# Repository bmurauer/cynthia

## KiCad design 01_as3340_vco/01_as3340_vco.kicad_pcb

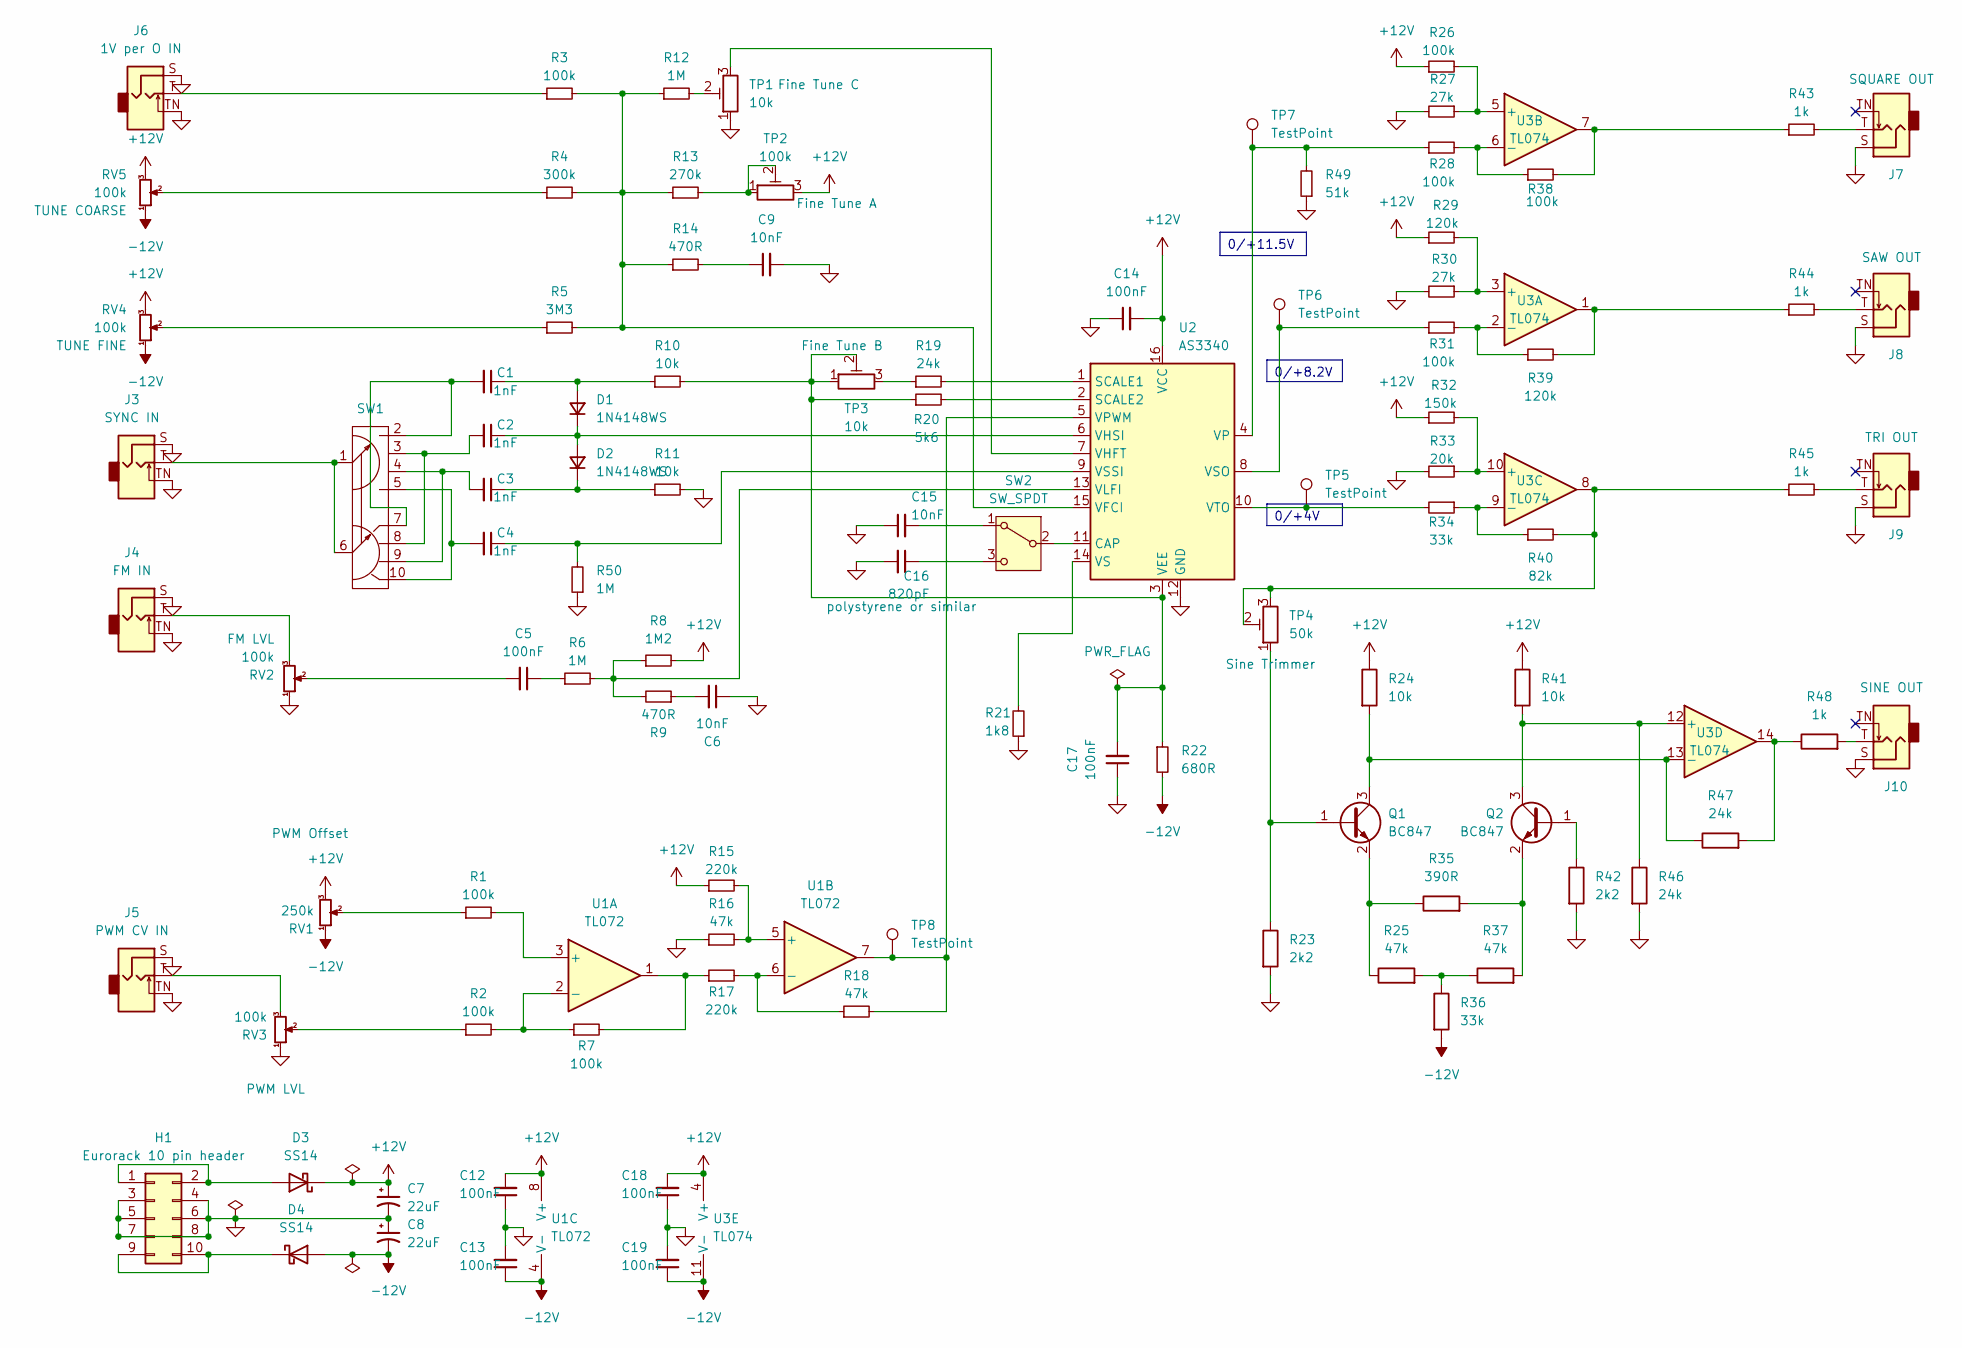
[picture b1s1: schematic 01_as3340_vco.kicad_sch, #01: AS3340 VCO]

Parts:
C1, C2, C3, C4: 1nF; C SMD 0805
C5, C12, C13, C14, C17, C18, C19: 100nF; C SMD 0805
C6, C9: 10nF; C SMD 0805
C7, C8: 22uF; CP_Radial_D6.3mm_P2.50mm
C15: 10nF; C_Disc_D10.5mm_W5.0mm_P10.00mm
C16: 820pF; C_Disc_D10.5mm_W5.0mm_P10.00mm
D1, D2: 1N4148WS; D_SOD-323_HandSoldering
D3, D4: SS14; D_SMA
H1: Eurorack 10 pin header; Eurorack Header
J3: SYNC IN; 3.5mm jack mono switched
J4: FM IN; 3.5mm jack mono switched
J5: PWM CV IN; 3.5mm jack mono switched
J6: 1V per O IN; 3.5mm jack mono switched
J7: SQUARE OUT; 3.5mm jack mono switched
J8: SAW OUT; 3.5mm jack mono switched
J9: TRI OUT; 3.5mm jack mono switched
J10: SINE OUT; 3.5mm jack mono switched
Q1, Q2: BC847; SOT-23
R1, R2, R3, R7, R26, R28, R31, R38: 100k; R SMD 0805
R4: 300k; R SMD 0805
R5: 3M3; R SMD 0805
R6, R12, R50: 1M; R SMD 0805
R8: 1M2; R SMD 0805
R9, R14: 470R; R SMD 0805
R10, R11, R24, R41: 10k; R SMD 0805
R13: 270k; R SMD 0805
R15, R17: 220k; R SMD 0805
R16, R18, R25, R37: 47k; R SMD 0805
R19, R46, R47: 24k; R SMD 0805
R20: 5k6; R SMD 0805
R21: 1k8; R SMD 0805
R22: 680R; R SMD 0805
R23, R42: 2k2; R SMD 0805
R27, R30: 27k; R SMD 0805
R29, R39: 120k; R SMD 0805
R32: 150k; R SMD 0805
R33: 20k; R SMD 0805
R34, R36: 33k; R SMD 0805
R35: 390R; R SMD 0805
R40: 82k; R SMD 0805
R43, R44, R45, R48: 1k; R SMD 0805
R49: 51k; R SMD 0805
RV1: 250k; potientiometer
RV2, RV3, RV4, RV5: 100k; potientiometer
SW1: switch_linear_2x4
SW2: SW_SPDT; switch_spdt
TP1, TP3: 10k; trimmer
TP2: 100k; trimmer
TP4: 50k; trimmer
TP5, TP6, TP7, TP8: TestPoint; TestPoint_Pad_1.0x1.0mm
U1: TL072; SOIC-8_3.9x4.9mm_P1.27mm
U2: AS3340; SOIC-16_3.9x9.9mm_P1.27mm
U3: TL074; SOIC-14_3.9x8.7mm_P1.27mm

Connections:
+12V: C7.1, C12.2, C14.2, C18.2, D3.1 (K), R8.2, R15.1, R24.1, R26.1, R29.1, R32.1, R41.1, RV1.3, RV4.3, RV5.3, TP2.3, U1.8 (V+), U2.16 (VCC), U3.4 (V+)
-12V: C8.2, C13.1, C19.1, D4.2 (A), R22.2, R36.2, RV1.1, RV4.1, RV5.1, U1.4 (V-), U3.11 (V-)
GND: C6.1, C7.2, C8.1, C9.2, C12.1, C13.2, C14.1, C15.1, C16.2, C17.1, C18.1, C19.2, H1.3, H1.4, H1.5, H1.6, H1.7, H1.8, J3.S, J3.TN, J4.S, J4.TN, J5.S, J5.TN, J6.S, J6.TN, J7.S, J8.S, J9.S, J10.S, R11.2, R16.1, R21.1, R23.2, R27.2, R30.2, R33.2, R42.2, R46.2, R49.1, R50.1, RV2.1, RV3.1, TP1.1, U2.12 (GND)
unnamed: C1.2, SW1.2, SW1.7
unnamed: C2.2, SW1.3, SW1.8
unnamed: C3.2, SW1.4, SW1.9
unnamed: C4.2, SW1.5, SW1.10
unnamed: C5.1, R6.1
unnamed: C5.2, RV2.2
unnamed: C6.2, R9.1
unnamed: C9.1, R14.2
unnamed: C1.1, D1.2 (A), R10.1
unnamed: C2.1, D1.1 (K), D2.2 (A), U2.6 (VHSI)
unnamed: C3.1, D2.1 (K), R11.1
unnamed: D3.2 (A), H1.1, H1.2
unnamed: D4.1 (K), H1.9, H1.10
unnamed: J3.T, SW1.1, SW1.6
unnamed: J4.T, RV2.3
unnamed: J5.T, RV3.3
unnamed: J6.T, R3.1
unnamed: J7.T, R43.2
unnamed: J8.T, R44.2
unnamed: J9.T, R45.2
unnamed: J10.T, R48.2
unnamed: Q1.1 (B), R23.1, TP4.1
unnamed: Q1.3 (C), R24.2, R47.1, U3.13 (-)
unnamed: Q1.2 (E), R25.1, R35.1
unnamed: Q2.1 (B), R42.1
unnamed: Q2.3 (C), R41.2, R46.1, U3.12 (+)
unnamed: Q2.2 (E), R35.2, R37.2
unnamed: R1.1, RV1.2
unnamed: R2.1, RV3.2
unnamed: R4.1, RV5.2
unnamed: R5.1, RV4.2
unnamed: R12.2, TP1.2
unnamed: R13.2, TP2.1, TP2.2
unnamed: R7.2, R17.1, U1.1
unnamed: R19.1, TP3.3
unnamed: R25.2, R36.1, R37.1
unnamed: R38.2, R43.1, U3.7
unnamed: R39.2, R44.1, U3.1
unnamed: R40.2, R45.1, TP4.2, TP4.3, U3.8
unnamed: R47.2, R48.1, U3.14
unnamed: C15.2, SW2.1 (A)
unnamed: SW2.2 (B), U2.11 (CAP)
unnamed: C16.1, SW2.3 (C)
unnamed: R1.2, U1.3 (+)
unnamed: R2.2, R7.1, U1.2 (-)
unnamed: R15.2, R16.2, U1.5 (+)
unnamed: R17.2, R18.1, U1.6 (-)
unnamed: R19.2, U2.1 (SCALE1)
unnamed: R20.2, U2.2 (SCALE2)
unnamed: C17.2, R10.2, R20.1, R22.1, TP3.1, TP3.2, U2.3 (VEE)
unnamed: R3.2, R4.2, R5.2, R12.1, R13.1, R14.1, U2.15 (VFCI)
unnamed: TP1.3, U2.7 (VHFT)
unnamed: R6.2, R8.1, R9.2, U2.13 (VLFI)
unnamed: R28.1, R49.2, TP7.1 (1_1), U2.4 (VP)
unnamed: R18.2, TP8.1 (1_1), U1.7, U2.5 (VPWM)
unnamed: R21.2, U2.14 (VS)
unnamed: R31.1, TP6.1 (1_1), U2.8 (VSO)
unnamed: C4.1, R50.2, U2.9 (VSSI)
unnamed: R34.2, TP5.1 (1_1), U2.10 (VTO)
unnamed: R29.2, R30.1, U3.3 (+)
unnamed: R31.2, R39.1, U3.2 (-)
unnamed: R26.2, R27.1, U3.5 (+)
unnamed: R28.2, R38.1, U3.6 (-)
unnamed: R32.2, R33.1, U3.10 (+)
unnamed: R34.1, R40.1, U3.9 (-)

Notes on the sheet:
0/+11.5V
0/+4V
0/+8.2V

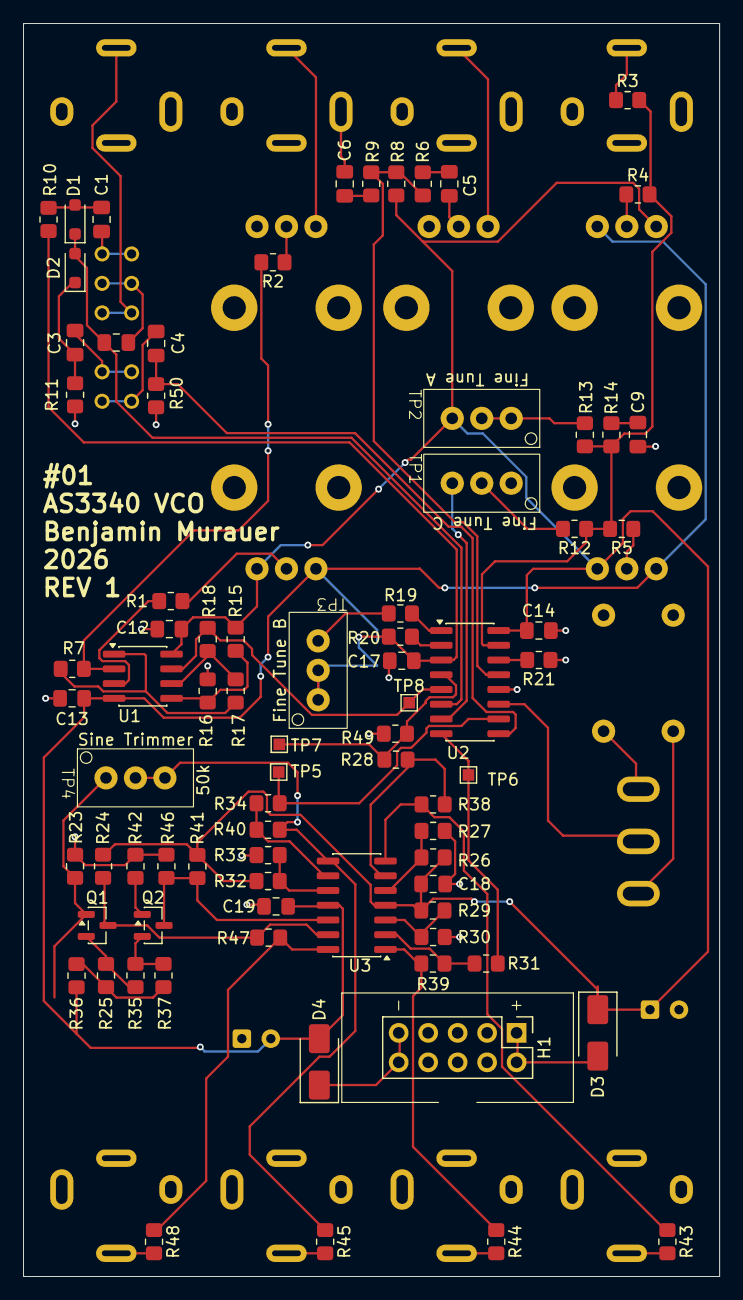
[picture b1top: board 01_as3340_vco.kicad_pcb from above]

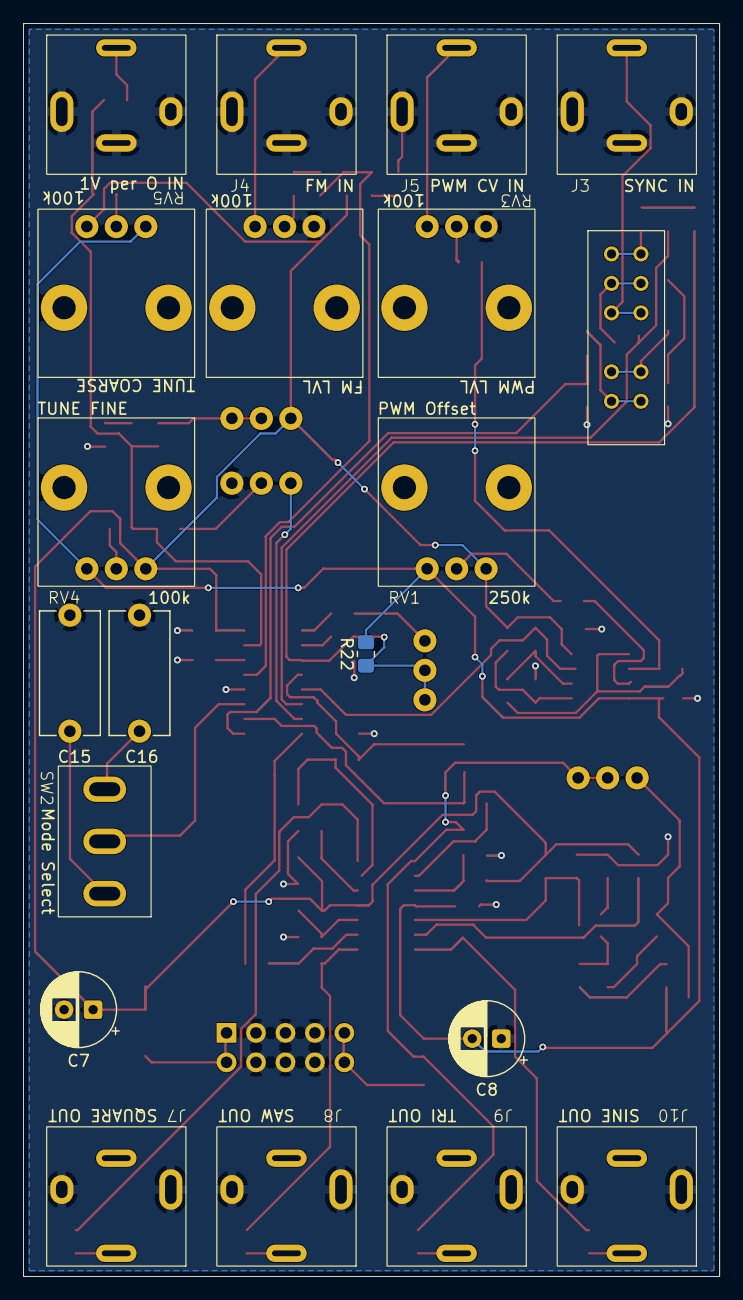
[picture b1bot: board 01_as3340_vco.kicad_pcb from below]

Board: 2 copper layers, 60.0 x 108.0 mm, 100 parts (20 on the bottom side), 68 nets.

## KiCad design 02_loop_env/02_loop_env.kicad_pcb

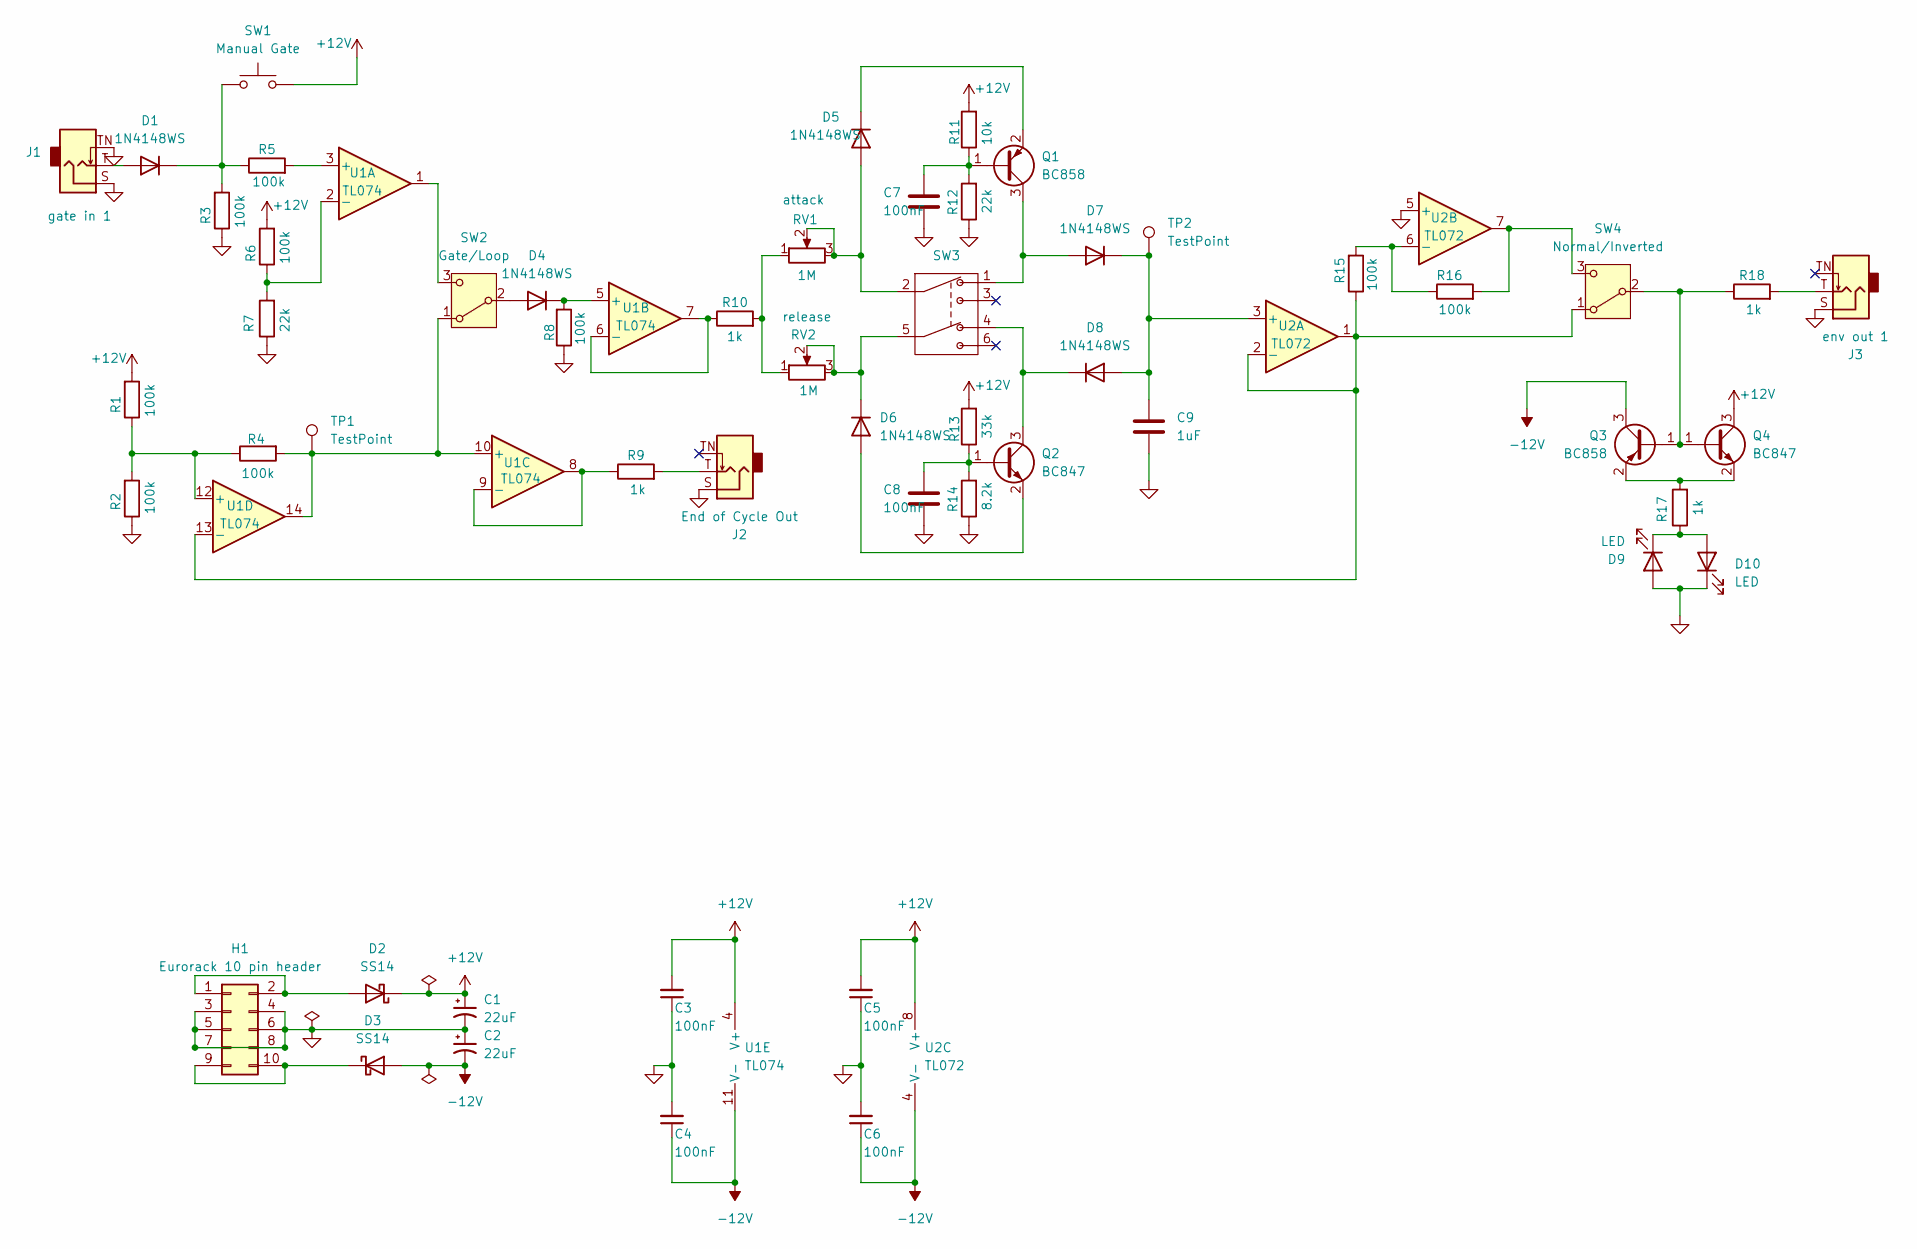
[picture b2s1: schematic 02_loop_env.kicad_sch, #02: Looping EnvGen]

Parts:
C1, C2: 22uF; CP_Radial_D6.3mm_P2.50mm
C3, C4, C5, C6, C7, C8: 100nF; C SMD 0805
C9: 1uF; C_Rect_L7.0mm_W6.5mm_P5.00mm
D1, D4, D5, D6, D7, D8: 1N4148WS; D_SOD-323_HandSoldering
D2, D3: SS14; D_SMA
D9, D10: LED; LED_D5.0mm
H1: Eurorack 10 pin header; Eurorack Header
J1: gate in 1; 3.5mm jack mono switched
J2: End of Cycle Out; 3.5mm jack mono switched
J3: env out 1; 3.5mm jack mono switched
Q1, Q3: BC858; SOT-23
Q2, Q4: BC847; SOT-23
R1, R2, R3, R4, R5, R6, R8, R15, R16: 100k; R SMD 0805
R7, R12: 22k; R SMD 0805
R9, R10, R17, R18: 1k; R SMD 0805
R11: 10k; R SMD 0805
R13: 33k; R SMD 0805
R14: 8.2k; R SMD 0805
RV1, RV2: 1M; potientiometer
SW1: Manual Gate; push button
SW2: Gate/Loop; switch_spdt
SW3: switch_dpdt
SW4: Normal/Inverted; switch_spdt
TP1, TP2: TestPoint; TestPoint_Pad_2.0x2.0mm
U1: TL074; SOIC-14_3.9x8.7mm_P1.27mm
U2: TL072; SOIC-8_3.9x4.9mm_P1.27mm

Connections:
+12V: C1.1, C3.2, C5.2, D2.1 (K), Q4.3 (C), R1.2, R6.2, R11.2, R13.2, SW1.2, U1.4 (V+), U2.8 (V+)
-12V: C2.2, C4.1, C6.1, D3.2 (A), Q3.3 (C), U1.11 (V-), U2.4 (V-)
GND: C1.2, C2.1, C3.1, C4.2, C5.1, C6.2, C7.2, C8.2, C9.2, D9.2 (A), D10.1 (K), H1.3, H1.4, H1.5, H1.6, H1.7, H1.8, J1.S, J1.TN, J2.S, J3.S, R2.1, R3.1, R7.1, R8.1, R12.1, R14.1, U2.5 (+)
unnamed: D1.2 (A), J1.T
unnamed: D1.1 (K), R3.2, R5.1, SW1.1
unnamed: D2.2 (A), H1.1, H1.2
unnamed: D3.1 (K), H1.9, H1.10
unnamed: D4.2 (A), SW2.2 (B)
unnamed: D4.1 (K), R8.2, U1.5 (+)
unnamed: D5.2 (A), RV1.2, RV1.3, SW3.2
unnamed: D5.1 (K), Q1.2 (E)
unnamed: D6.2 (A), Q2.2 (E)
unnamed: D6.1 (K), RV2.2, RV2.3, SW3.5
unnamed: D7.2 (A), Q1.3 (C), SW3.1
unnamed: C9.1, D7.1 (K), D8.2 (A), TP2.1 (1_1), U2.3 (+)
unnamed: D8.1 (K), Q2.3 (C), SW3.4
unnamed: D9.1 (K), D10.2 (A), R17.1
unnamed: J2.T, R9.2
unnamed: J3.T, R18.2
unnamed: C7.1, Q1.1 (B), R11.1, R12.2
unnamed: C8.1, Q2.1 (B), R13.1, R14.2
unnamed: Q3.1 (B), Q4.1 (B), R18.1, SW4.2 (B)
unnamed: Q3.2 (E), Q4.2 (E), R17.2
unnamed: R10.2, RV1.1, RV2.1
unnamed: R4.2, SW2.1 (A), TP1.1 (1_1), U1.10 (+), U1.14
unnamed: SW2.3 (C), U1.1
unnamed: R15.1, SW4.1 (A), U1.13 (-), U2.1, U2.2 (-)
unnamed: R16.2, SW4.3 (C), U2.7
unnamed: R5.2, U1.3 (+)
unnamed: R6.1, R7.2, U1.2 (-)
unnamed: R10.1, U1.6 (-), U1.7
unnamed: R9.1, U1.8, U1.9 (-)
unnamed: R1.1, R2.2, R4.1, U1.12 (+)
unnamed: R15.2, R16.1, U2.6 (-)

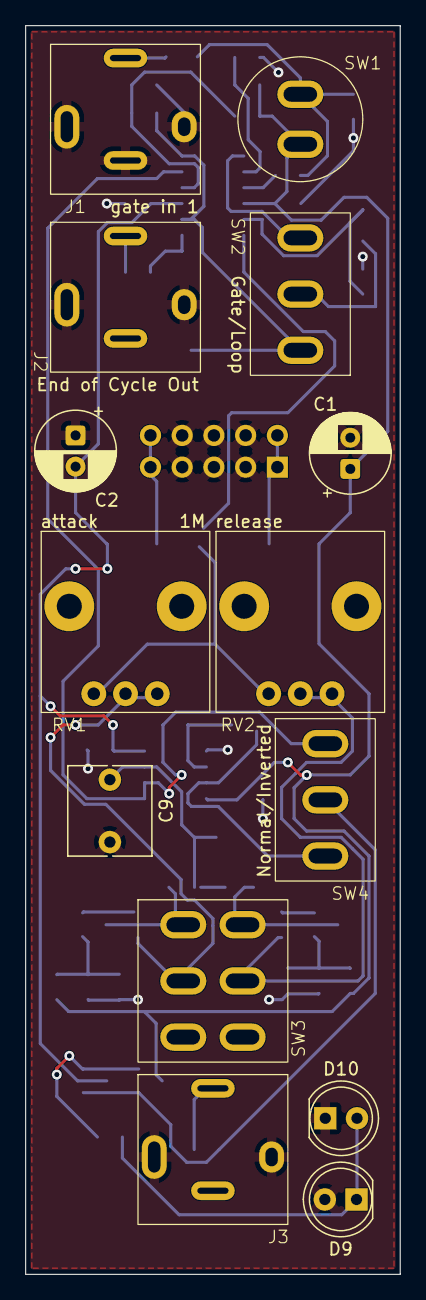
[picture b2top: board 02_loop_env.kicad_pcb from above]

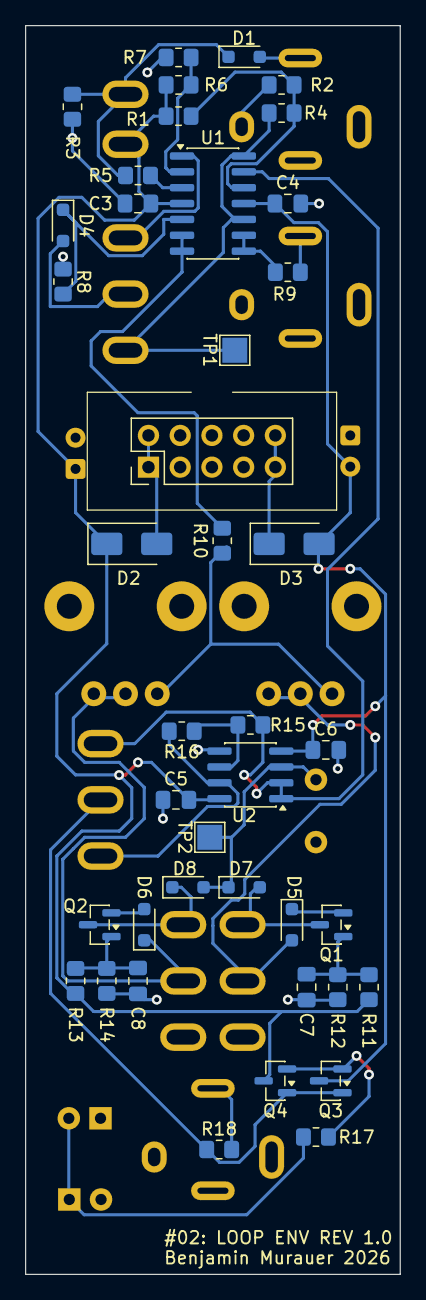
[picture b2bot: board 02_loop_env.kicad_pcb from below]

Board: 2 copper layers, 30.0 x 100.0 mm, 55 parts (41 on the bottom side), 34 nets.

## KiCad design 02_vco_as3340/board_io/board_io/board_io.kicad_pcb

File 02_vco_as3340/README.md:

# AS3340-based VCO: "Oh, Silly!"

This design is based on the [design from Eddy Bergman](https://www.eddybergman.com/2020/01/synthesizer-build-part-18-really-good.html), which is based on a DigiSound 80 VCO.

I have made the following modifications to it:

 - I have included a switch that changes the 1nF capacitor to a 10nF one, allowing for mad slow LFO action.
 - the output stages are modified so that the VCO roughly produces -5V/+5V outputs (instead of 0/+10V).
 - the design includes a sine wave output. This is based on Eddy Bergmans Triangle to Sine converter.
 - the triangle wave has a dedicated centering trimmer, as I thought that centering the signal is essential for the sine wave conversion - I think if you measure your resistors a bit, you should be able to do without the trimmer.
 - the PWM input stage uses one less op amp. For the PWM signal, the polarity of the CV signal is irrelevant, as (1) there is no fixed notion what "positive PWM" looks like in the output wave, and (2) the two different resulting options sound the same to the human ear. If you have a certain setup for LFOs in mind where this detail is important, note that the signal may be inverted before being put into the AS3340 chip.
 - the design does not include a zener diode, as the square wave is centered and scaled like the other stages.
 - I removed the second 1V/O CV input, as I personally don't to use it. The FM input is plenty for me.

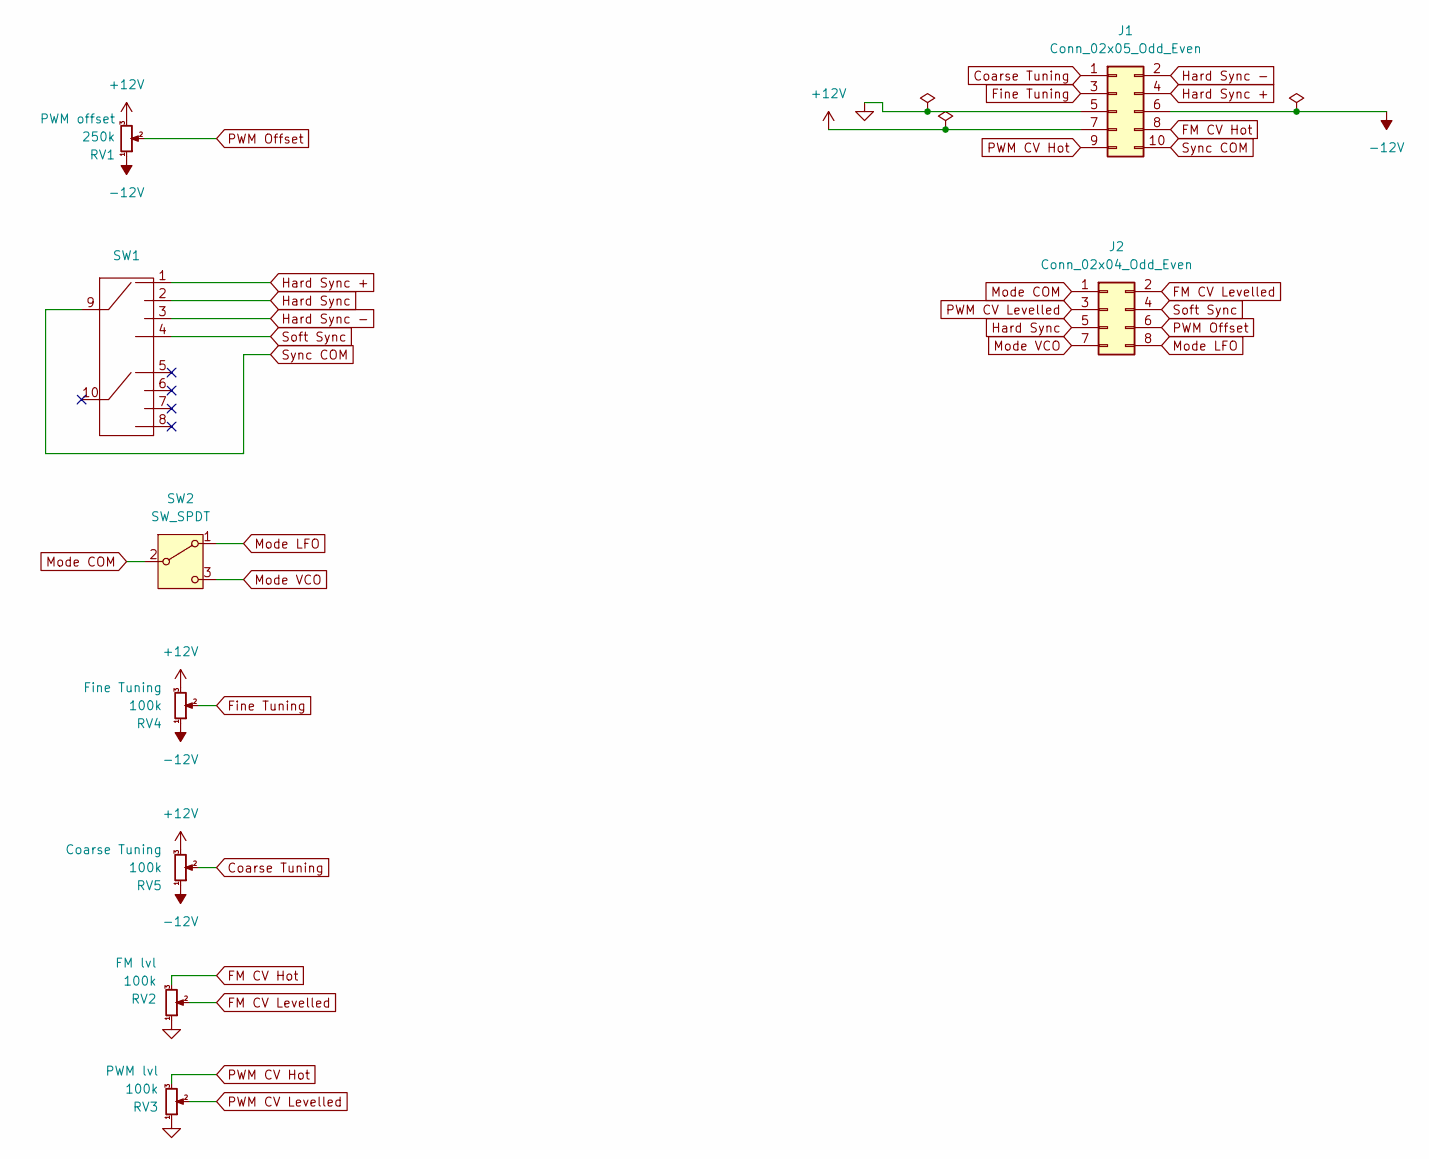
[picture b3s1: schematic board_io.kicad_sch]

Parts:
J1: Conn_02x05_Odd_Even; PinHeader_2x05_P2.54mm_Vertical
J2: Conn_02x04_Odd_Even; PinHeader_2x04_P2.54mm_Vertical
RV1: 250k; pot
RV2, RV3, RV4, RV5: 100k; pot
SW1: mini rotary switch
SW2: SW_SPDT; mini switch

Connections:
+12V: J1.7, RV1.3, RV4.3, RV5.3
-12V: J1.6, RV1.1, RV4.1, RV5.1
Coarse Tuning: J1.1, RV5.2
FM CV Hot: J1.8, RV2.3
FM CV Levelled: J2.2, RV2.2
Fine Tuning: J1.3, RV4.2
GND: J1.5, RV2.1, RV3.1
Hard Sync: J2.5, SW1.2
Hard Sync +: J1.4, SW1.1
Hard Sync -: J1.2, SW1.3
Mode COM: J2.1, SW2.2 (B)
Mode LFO: J2.8, SW2.1 (A)
Mode VCO: J2.7, SW2.3 (C)
PWM CV Hot: J1.9, RV3.3
PWM CV Levelled: J2.3, RV3.2
PWM Offset: J2.6, RV1.2
Soft Sync: J2.4, SW1.4
Sync COM: J1.10, SW1.9

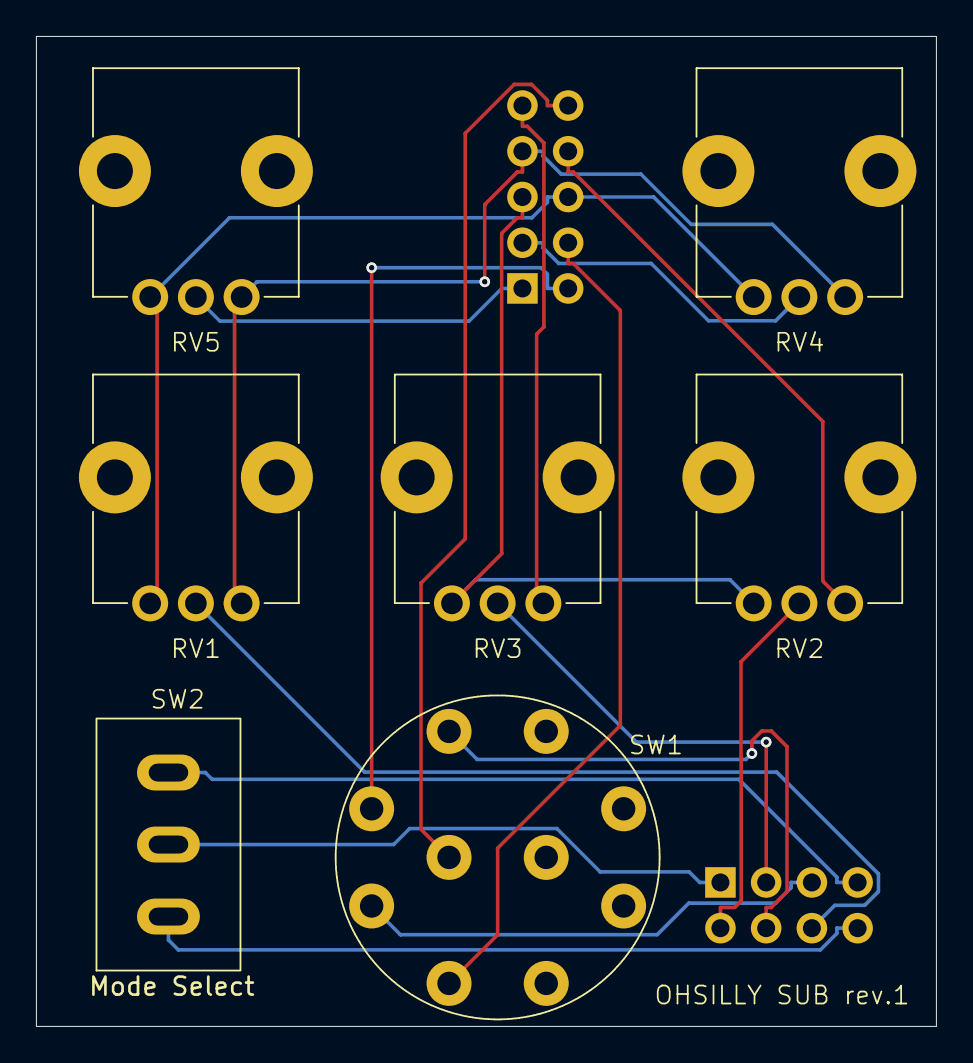
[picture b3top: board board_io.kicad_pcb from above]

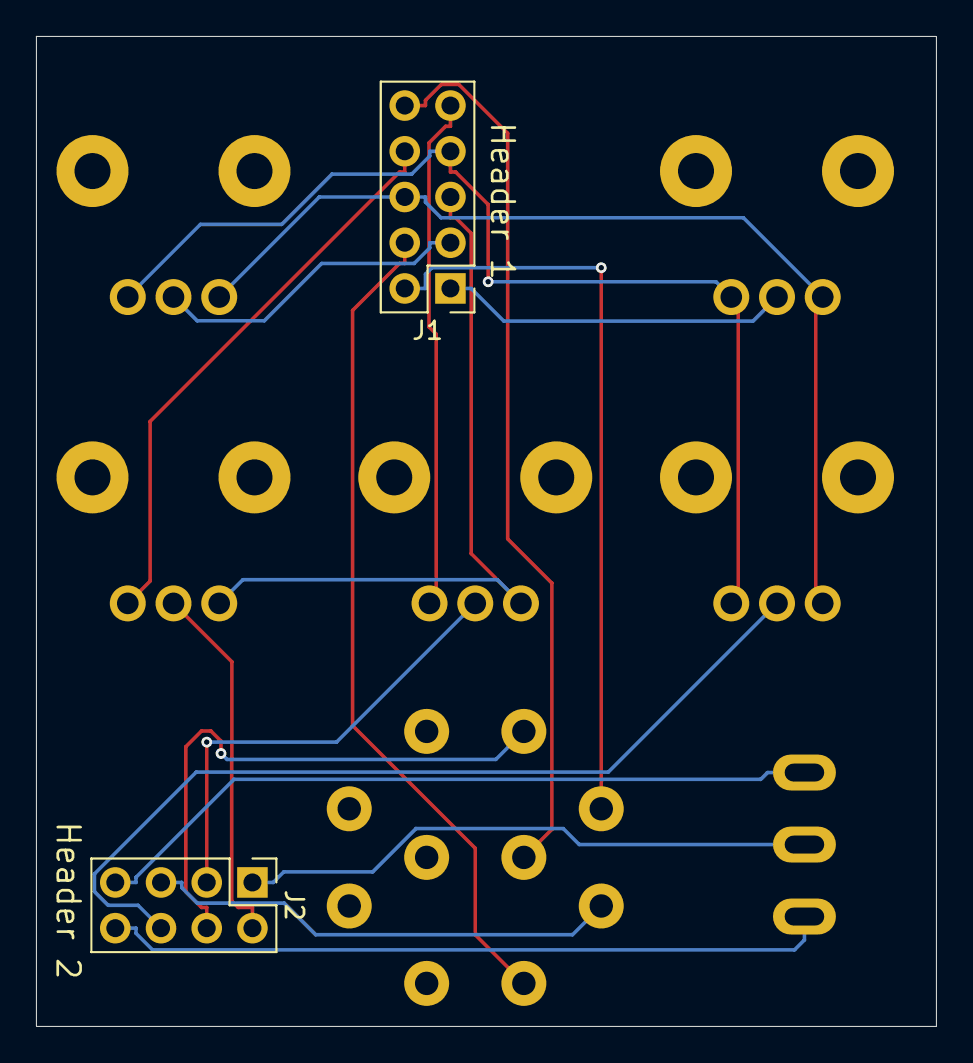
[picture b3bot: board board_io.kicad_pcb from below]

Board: 2 copper layers, 50.0 x 55.0 mm, 9 parts (2 on the bottom side), 18 nets.

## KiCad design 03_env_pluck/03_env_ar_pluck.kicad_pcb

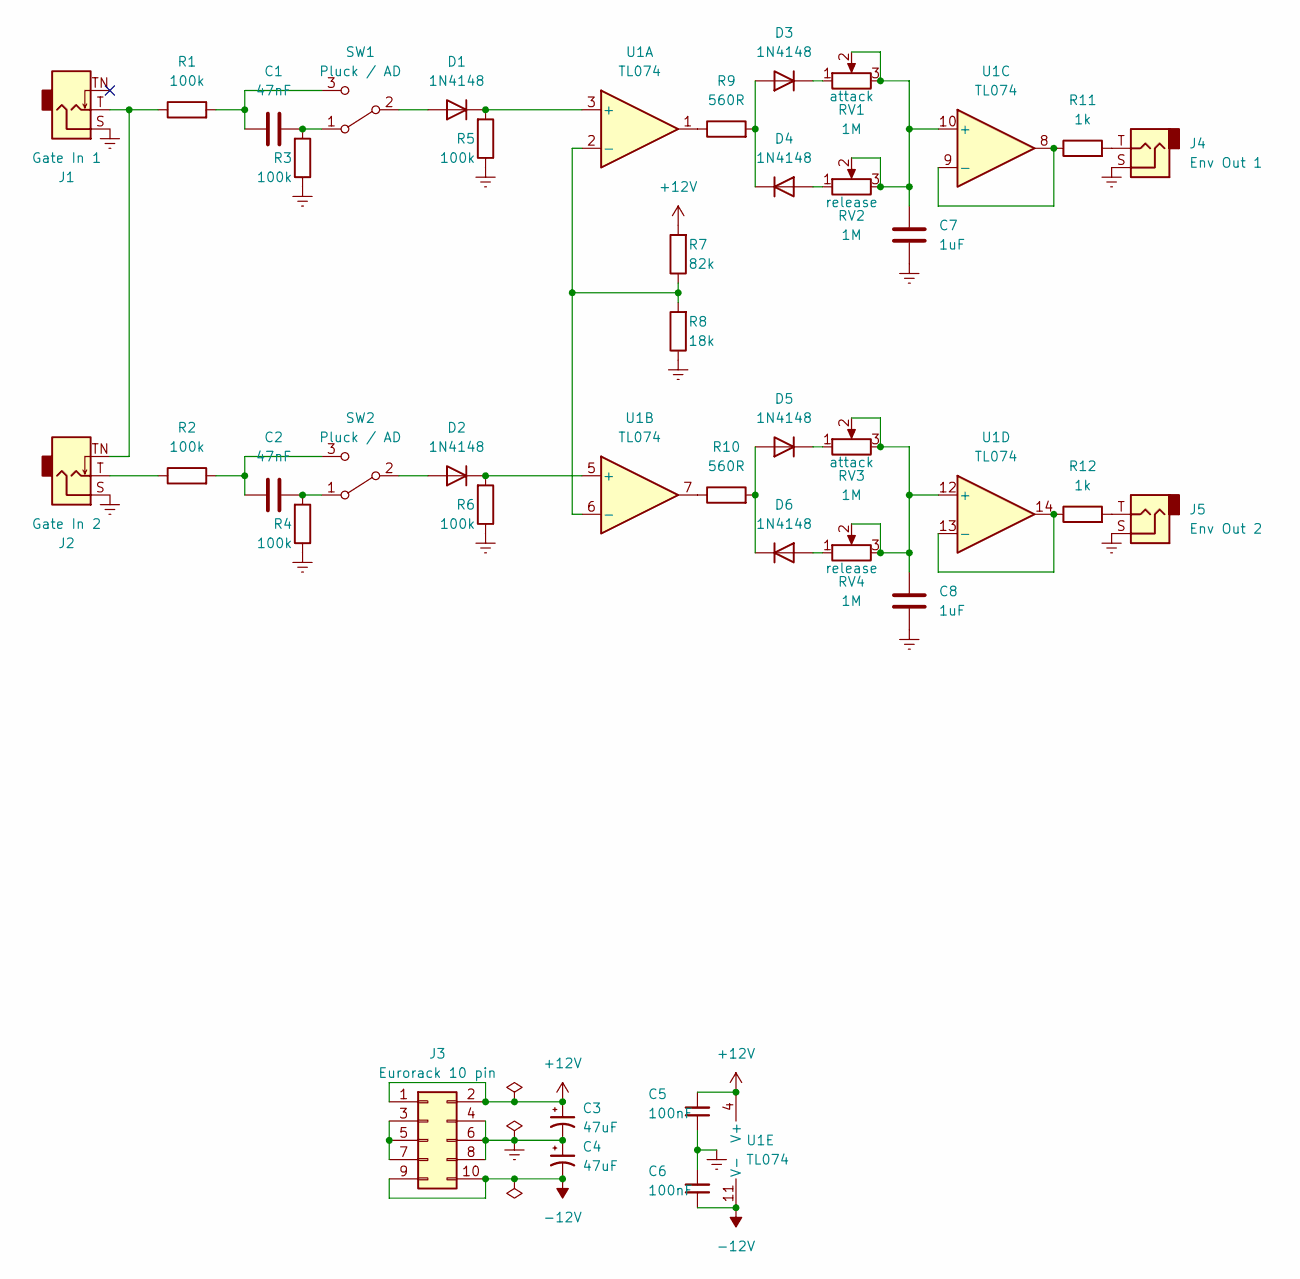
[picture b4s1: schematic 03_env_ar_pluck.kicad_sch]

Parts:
C1, C2: 47nF; C_Rect_L7.0mm_W2.5mm_P5.00mm
C3, C4: 47uF; CP_Radial_D6.3mm_P2.50mm
C5, C6: 100nF; C_Disc_D6.0mm_W2.5mm_P5.00mm
C7, C8: 1uF; C_Rect_L7.0mm_W2.5mm_P5.00mm
D1, D2, D3, D4, D5, D6: 1N4148; D_T-1_P10.16mm_Horizontal
J1: Gate In 1; Jack_6.35mm_Neutrik_NJ5FD-V_Vertical
J2: Gate In 2; Jack_6.35mm_Neutrik_NJ5FD-V_Vertical
J3: Eurorack 10 pin; PinHeader_2x05_P2.54mm_Vertical
J4: Env Out 1; Jack_6.35mm_Neutrik_NJ5FD-V_Vertical
J5: Env Out 2; Jack_6.35mm_Neutrik_NJ5FD-V_Vertical
R1, R2, R3, R4, R5, R6: 100k; R_Axial_DIN0207_L6.3mm_D2.5mm_P10.16mm_Horizontal
R7: 82k; R_Axial_DIN0207_L6.3mm_D2.5mm_P10.16mm_Horizontal
R8: 18k; R_Axial_DIN0207_L6.3mm_D2.5mm_P10.16mm_Horizontal
R9, R10: 560R; R_Axial_DIN0207_L6.3mm_D2.5mm_P10.16mm_Horizontal
R11, R12: 1k; R_Axial_DIN0207_L6.3mm_D2.5mm_P10.16mm_Horizontal
RV1, RV2, RV3, RV4: 1M; Potentiometer_Alpha_RD901F-40-00D_Single_Vertical
SW1, SW2: Pluck / AD; PinHeader_1x03_P2.54mm_Vertical
U1: TL074; DIP-14_W7.62mm

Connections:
+12V: C3.1, C5.2, J3.1, J3.2, R7.2, U1.4 (V+)
-12V: C4.2, C6.1, J3.9, J3.10, U1.11 (V-)
GNDREF: C3.2, C4.1, C5.1, C6.2, C7.2, C8.2, J1.S, J2.S, J3.4, J3.6, J3.8, J4.S, J5.S, R3.1, R4.1, R5.1, R6.1, R8.1
unnamed: D1.2 (A), SW1.2 (B)
unnamed: D1.1 (K), R5.2, U1.3 (+)
unnamed: D2.2 (A), SW2.2 (B)
unnamed: D2.1 (K), R6.2, U1.5 (+)
unnamed: D3.2 (A), D4.1 (K), R9.2
unnamed: D3.1 (K), RV1.1
unnamed: D4.2 (A), RV2.1
unnamed: D5.2 (A), D6.1 (K), R10.2
unnamed: D5.1 (K), RV3.1
unnamed: D6.2 (A), RV4.1
unnamed: J1.T, J2.TN, R1.1
unnamed: J2.T, R2.1
unnamed: J3.3, J3.5, J3.7
unnamed: J4.T, R11.2
unnamed: J5.T, R12.2
unnamed: R9.1, U1.1
unnamed: R10.1, U1.7
unnamed: C1.2, R3.2, SW1.1 (A)
unnamed: C1.1, R1.2, SW1.3 (C)
unnamed: C2.2, R4.2, SW2.1 (A)
unnamed: C2.1, R2.2, SW2.3 (C)
unnamed: R7.1, R8.2, U1.2 (-), U1.6 (-)
unnamed: C7.1, RV1.2, RV1.3, RV2.2, RV2.3, U1.10 (+)
unnamed: R11.1, U1.8, U1.9 (-)
unnamed: C8.1, RV3.2, RV3.3, RV4.2, RV4.3, U1.12 (+)
unnamed: R12.1, U1.13 (-), U1.14

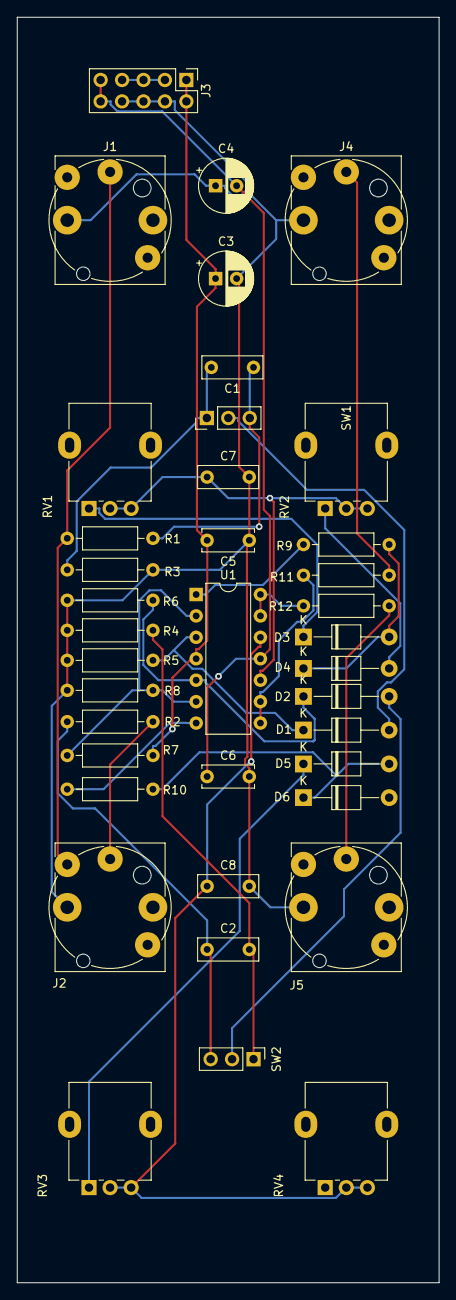
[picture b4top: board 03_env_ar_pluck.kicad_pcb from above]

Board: 2 copper layers, 50.0 x 150.0 mm, 38 parts (0 on the bottom side), 29 nets.
